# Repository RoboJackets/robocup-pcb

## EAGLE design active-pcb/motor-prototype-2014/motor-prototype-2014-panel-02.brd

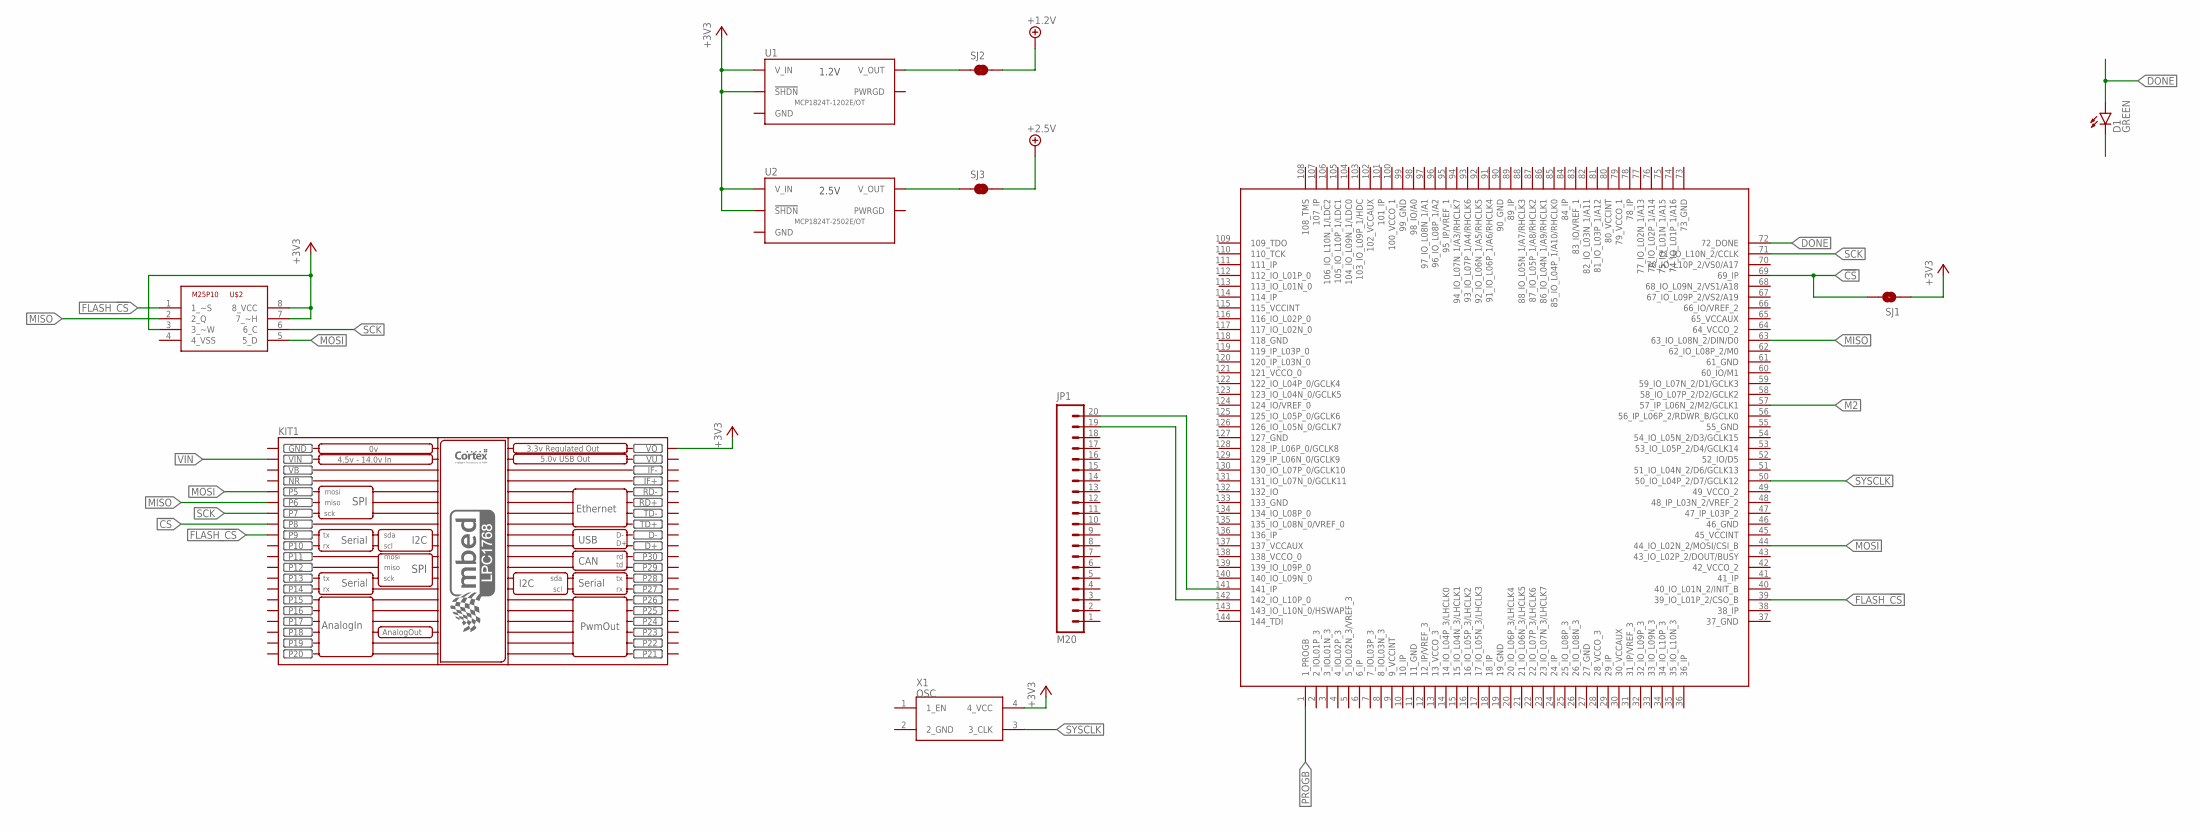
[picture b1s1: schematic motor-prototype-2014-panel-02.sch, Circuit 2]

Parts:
D1: GREEN; LED-0603
JP1: M20; 1X20
KIT1: MBED_NXP_LPC1768; MBED-KIT
SJ1: JUMPER-PAD-2-NO; PAD-JUMPER-2-NO_NO_SILK
SJ2, SJ3: JUMPER-PAD-2-NC_BY_TRACE; PAD-JUMPER-2-NC_BY_TRACE_YES_SILK
U1: MCP1824T-1202E/OT; SOT-23-5
U2: MCP1824T-2502E/OT; SOT-23-5
U$1: XC3S_TQ144; TQFP144
U$2: M25P10; SO08
X1: OSC; XTAL_LCC

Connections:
!CS!: KIT1.P$8 (P8), SJ1.2, U$1.69 (69_IP)
+1.2V: SJ2.2
+2.5V: SJ3.2
+3V3: KIT1.VOUT (VO), SJ1.1, U1.1 (V_IN), U1.3 (!SHDN), U2.1 (V_IN), U2.3 (!SHDN), U$2.3 (3_~W), U$2.7 (7_~H), U$2.8 (8_VCC), X1.4 (4_VCC)
DONE: D1.A, U$1.72 (72_DONE)
FLASH_!CS!: KIT1.P$9 (P9), U$1.39 (39_IO_L01P_2/CSO_B), U$2.1 (1_~S)
GND: KIT1.GND
M2: U$1.57 (57_IP_L06N_2/M2/GCLK1)
MISO: KIT1.P$6 (P6), U$1.63 (63_IO_L08N_2/DIN/D0), U$2.2 (2_Q)
MOSI: KIT1.P$5 (P5), U$1.44 (44_IO_L02N_2/MOSI/CSI_B), U$2.5 (5_D)
unnamed: JP1.20, U$1.141 (141_IP)
unnamed: JP1.19, U$1.142 (142_IO_L10P_0)
PROGB: U$1.1 (1_PROGB)
SCK: KIT1.P$7 (P7), U$1.71 (71_IO_L10N_2/CCLK), U$2.6 (6_C)
SYSCLK: U$1.50 (50_IO_L04P_2/D7/GCLK12), X1.3 (3_CLK)
VB: KIT1.VB
VIN: KIT1.VIN
VU: KIT1.VU
V_OUT: SJ2.1, SJ3.1, U1.5 (V_OUT), U2.5 (V_OUT)

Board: 4 copper layers, 11 parts (2 on the bottom side), 11 nets, no tracks yet.

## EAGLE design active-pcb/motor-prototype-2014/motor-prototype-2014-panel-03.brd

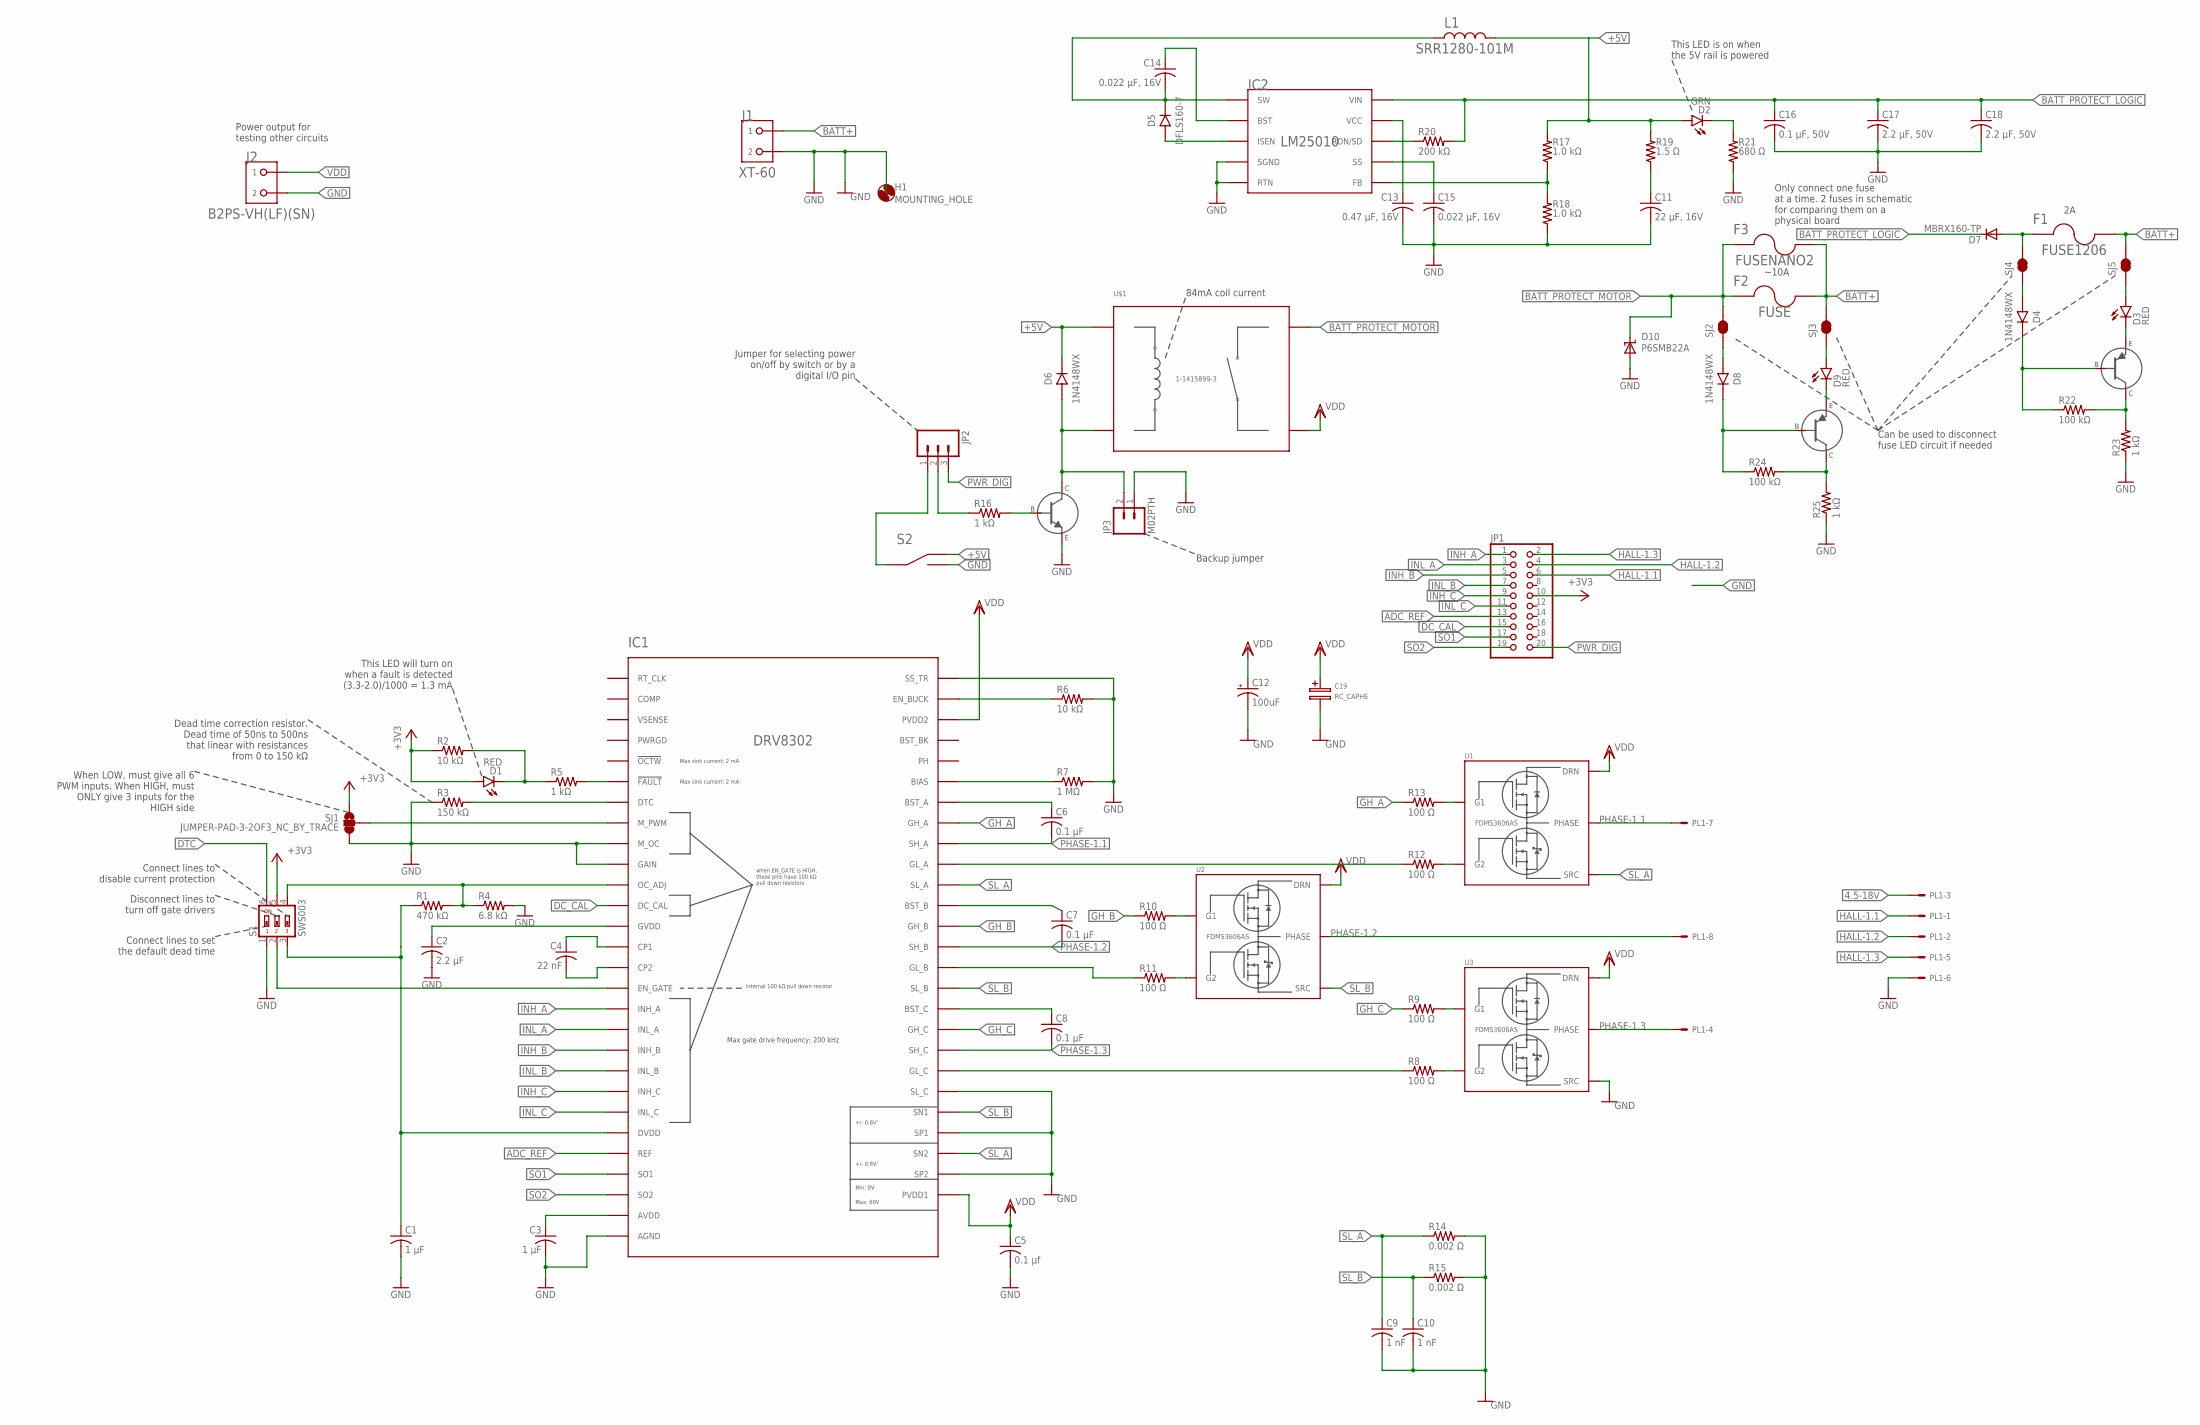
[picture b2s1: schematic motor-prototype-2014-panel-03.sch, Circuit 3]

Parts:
C1, C3: 1 µF; C0603
C2: 2.2 µF; C0603
C4: 22 nF; C1206
C5: 0.1 µf; C0603
C6, C7, C8: 0.1 µF; C0402
C9, C10: 1 nF; C0402
C11: 22 µF, 16V; C0402
C12: 100uF; PANASONIC_H13
C13: 0.47 µF, 16V; C0402
C14, C15: 0.022 µF, 16V; C0402
C16: 0.1 µF, 50V; C0603
C17, C18: 2.2 µF, 50V; C0603
C19: RC_CAPHE; HE_SERIES
D1, D3, D9: RED; LED-0603
D2: GRN; LED-0603
D4, D6, D8: 1N4148WX; SOD-323
D5: DFLS160-7; POWERDI-123
D7: MBRX160-TP; SOD123
D10: P6SMB22A; SMBJ
F1: FUSE1206; F1206
F2: FUSE; FUSE_MINI_ATC
F3: FUSENANO2; NANO2_157
H1: MOUNTING_HOLE
IC1: DRV8302; TSSOP-56_3
IC2: LM25010; 10-WDFN
J1: XT-60
J2: B2PS-VH(LF)(SN); B2PS
JP1: PINHD-2X10; 2X10
JP2: M03PTH; 1X03
JP3: M02PTH; 1X02
L1: SRR1280-101M; SRR1280
PL1: 555X-8V; 5566-8
Q1, Q3: BJT-PNP_; SOT-23-3
Q2: MMBT2222A-TP; SOT-23-3
R1: 470 kΩ; R0402
R2, R6: 10 kΩ; R0402
R3: 150 kΩ; R0603
R4: 6.8 kΩ; R0402
R5, R16, R23, R25: 1 kΩ; R0402
R7: 1 MΩ; R0402
R8, R9, R10, R11, R12, R13: 100 Ω; R0402
R14, R15: 0.002 Ω; R1206
R17, R18: 1.0 kΩ; R0402
R19: 1.5 Ω; R0402
R20: 200 kΩ; R0402
R21: 680 Ω; R0402
R22, R24: 100 kΩ; R0402
S1: SWS003; SMS-003
S2: 34EWMSP12MRT; 34EWMSP12M6RT
SJ1: JUMPER-PAD-3-2OF3_NC_BY_TRACE; PAD-JUMPER-3-2OF3_NC_BY_TRACE_YES_SILK_FULL_BOX
SJ2, SJ3, SJ4, SJ5: JUMPER-PAD-2-NC_BY_TRACE; PAD-JUMPER-2-NC_BY_TRACE_YES_SILK
U1, U2, U3: FDMS3606AS; PQFN-(DUAL)
U$1: 1-1415899-3

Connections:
4.5-18V: PL1.3
!FAULT!: IC1.6 (!FAULT!), R5.2
+3V3: D1.A, JP1.10, R2.1, S1.5, SJ1.1
+5V: D2.A, D6.C, L1.P$1, R17.2, R19.2, S2.1 (OFF), U$1.A1 (2)
ADC_REF: IC1.24 (REF), JP1.13
BATT+: F1.2, F2.2.1 (2), F2.2.2 (2), F3.P$2 (2), J1.BATT (1), SJ3.2, SJ5.2
BATT_PROTECT_LOGIC: C16.1, C17.1, C18.1, D7.C, IC2.P10.1 (VIN), IC2.P10.2 (VIN), R20.2
BATT_PROTECT_MOTOR: D10.C, F2.1.1 (1), F2.1.2 (1), F3.P$1 (1), SJ2.2, U$1.14.1 (3), U$1.14.2 (3)
BIAS: IC1.49 (BIAS), R7.1
BOB: D7.A, F1.1, SJ4.2
BST_A: C6.1, IC1.48 (BST_A)
BST_B: C7.1, IC1.43 (BST_B)
BST_BK: IC1.52 (BST_BK)
BST_C: C8.1, IC1.38 (BST_C)
CP1: C4.1, IC1.14 (CP1)
CP2: C4.2, IC1.15 (CP2)
DC_CAL: IC1.12 (DC_CAL), JP1.15
DTC: IC1.7 (DTC), R3.2, S1.6
GH_A: IC1.47 (GH_A), R13.1
GH_A_F: R13.2, U1.1 (G1)
GH_B: IC1.42 (GH_B), R10.1
GH_B_F: R10.2, U2.1 (G1)
GH_C: IC1.37 (GH_C), R9.1
GH_C_F: R9.2, U3.1 (G1)
GL_A: IC1.45 (GL_A), R12.1
GL_A_F: R12.2, U1.8 (G2)
GL_B: IC1.40 (GL_B), R11.1
GL_B_F: R11.2, U2.8 (G2)
GL_C: R8.2, U3.8 (G2)
GND: C1.2, C2.2, C3.2, C5.2, C9.2, C10.2, C11.2, C12.-, C13.2, C15.2, C16.2, C17.2, C18.2, C19.NEG (-), D10.A, H1.GND, IC1.9 (M_OC), IC1.10 (GAIN), IC1.28 (AGND), IC1.30 (SP2), IC1.32 (SP1), IC1.34 (SL_C), IC1.56 (SS_TR), IC1.57 (AGND), IC1.58 (AGND), IC1.59 (AGND), IC2.P4.1 (SGND), IC2.P4.2 (SGND), IC2.P5.1 (RTN), IC2.P5.2 (RTN), IC2.P_CENTER (SGND), J1.GND (2), J2.2, JP3.1, PL1.6, Q2.S (E), R3.1, R4.2, R6.2, R7.2, R14.2, R15.2, R18.1, R21.1, R23.1, R25.1, S1.1, S2.3 (ON), SJ1.3, U3.5 (SRC), U3.6 (SRC), U3.7 (SRC)
HALL-1.1: JP1.6, PL1.1
HALL-1.2: JP1.4, PL1.2
HALL-1.3: JP1.2, PL1.5
INH_A: IC1.17 (INH_A), JP1.1
INH_B: IC1.19 (INH_B), JP1.5
INH_C: IC1.21 (INH_C), JP1.9
INL_A: IC1.18 (INL_A), JP1.3
INL_B: IC1.20 (INL_B), JP1.7
INL_C: IC1.22 (INL_C), JP1.11
M_PWM: IC1.8 (M_PWM), SJ1.2
unnamed: D1.C, R2.2, R5.1
unnamed: C15.1, IC2.P7.1 (SS), IC2.P7.2 (SS)
unnamed: JP2.2, R16.1
unnamed: IC1.35 (GL_C), R8.1
unnamed: D5.A, IC2.P3.1 (ISEN), IC2.P3.2 (ISEN)
unnamed: C13.1, IC2.P9.1 (VCC), IC2.P9.2 (VCC)
unnamed: D4.C, Q1.G (B), R22.1
unnamed: IC1.11 (OC_ADJ), R1.2, R4.1, S1.4
unnamed: IC2.P6.1 (FB), IC2.P6.2 (FB), R17.1, R18.2
unnamed: C2.1, IC1.13 (GVDD)
unnamed: C1.1, IC1.23 (DVDD), R1.1, S1.3
unnamed: IC1.55 (EN_BUCK), R6.1
unnamed: IC1.16 (EN_GATE), S1.2
unnamed: C3.1, IC1.27 (AVDD)
unnamed: D3.C, Q1.S (E)
unnamed: IC2.P8.1 (RON/SD), IC2.P8.2 (RON/SD), R20.1
unnamed: Q1.D (C), R22.2, R23.2
unnamed: C11.1, R19.1
unnamed: D9.C, Q3.S (E)
unnamed: C14.1, IC2.P2.1 (BST), IC2.P2.2 (BST)
unnamed: C14.2, D5.C, IC2.P1.1 (SW), IC2.P1.2 (SW), L1.P$2
unnamed: D6.A, JP3.2, Q2.D (C), U$1.A2 (6)
unnamed: D2.C, R21.2
unnamed: Q2.G (B), R16.2
unnamed: D8.C, Q3.G (B), R24.1
unnamed: Q3.D (C), R24.2, R25.2
unnamed: JP2.1, S2.2 (C)
unnamed: D8.A, SJ2.1
unnamed: D9.A, SJ3.1
unnamed: D4.A, SJ4.1
unnamed: D3.A, SJ5.1
PHASE-1.1: C6.2, IC1.46 (SH_A), PL1.7, U1.CENTER (PHASE)
PHASE-1.2: C7.2, IC1.41 (SH_B), PL1.8, U2.CENTER (PHASE)
PHASE-1.3: C8.2, IC1.36 (SH_C), PL1.4, U3.CENTER (PHASE)
PWR_DIG: JP1.20, JP2.3
SL_A: C9.1, IC1.31 (SN2), IC1.44 (SL_A), R14.1, U1.5 (SRC), U1.6 (SRC), U1.7 (SRC)
SL_B: C10.1, IC1.33 (SN1), IC1.39 (SL_B), R15.1, U2.5 (SRC), U2.6 (SRC), U2.7 (SRC)
SO1: IC1.25 (SO1), JP1.17
SO2: IC1.26 (SO2), JP1.19
VDD: C5.1, C12.+, C19.POS (+), IC1.29 (PVDD1), IC1.53 (PVDD2), IC1.54 (PVDD2), J2.1, U1.2 (DRN), U1.3 (DRN), U1.4 (DRN), U1.LARGE_1 (DRN), U1.LARGE_2 (DRN), U1.LARGE_3 (DRN), U2.2 (DRN), U2.3 (DRN), U2.4 (DRN), U2.LARGE_1 (DRN), U2.LARGE_2 (DRN), U2.LARGE_3 (DRN), U3.2 (DRN), U3.3 (DRN), U3.4 (DRN), U3.LARGE_1 (DRN), U3.LARGE_2 (DRN), U3.LARGE_3 (DRN), U$1.11.1 (5), U$1.11.2 (5)

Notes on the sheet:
Connect lines to disable current protection
Dead time correction resistor. Dead time of 50ns to 500ns that linear with resistances from 0 to 150 kΩ
Disconnect lines to turn off gate drivers
Connect lines to set the default dead time
This LED is on when the 5V rail is powered
This LED will turn on when a fault is detected (3.3-2.0)/1000 = 1.3 mA
When LOW, must give all 6 PWM inputs. When HIGH, must ONLY give 3 inputs for the HIGH side
84mA coil current
Backup jumper
Jumper for selecting power on/off by switch or by a digital I/O pin
Can be used to disconnect fuse LED circuit if needed
~10A
Only connect one fuse at a time. 2 fuses in schematic for comparing them on a physical board
Power output for testing other circuits

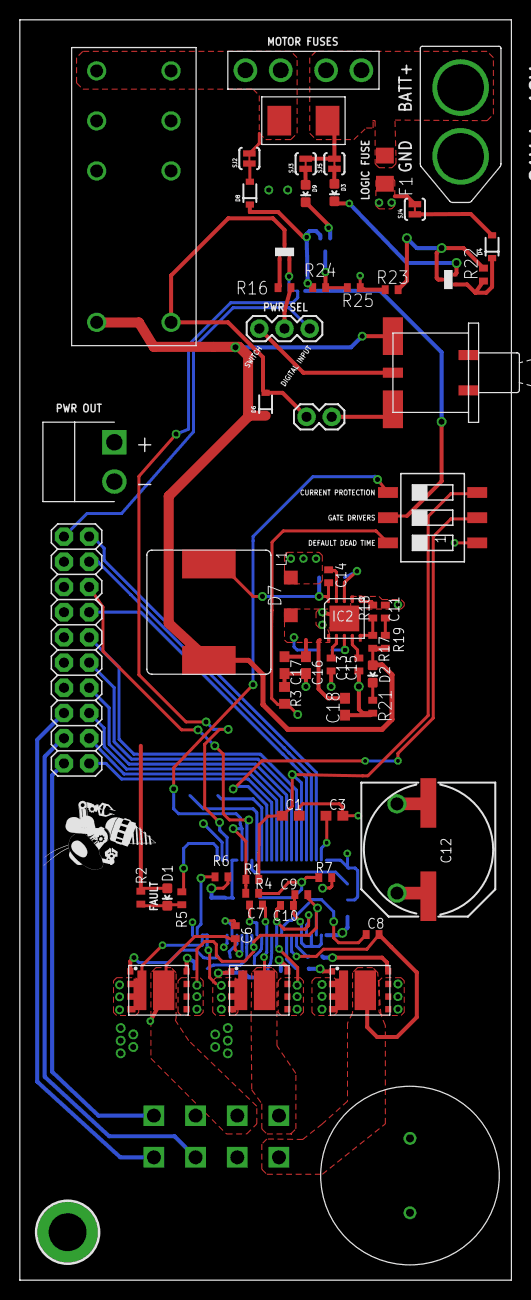
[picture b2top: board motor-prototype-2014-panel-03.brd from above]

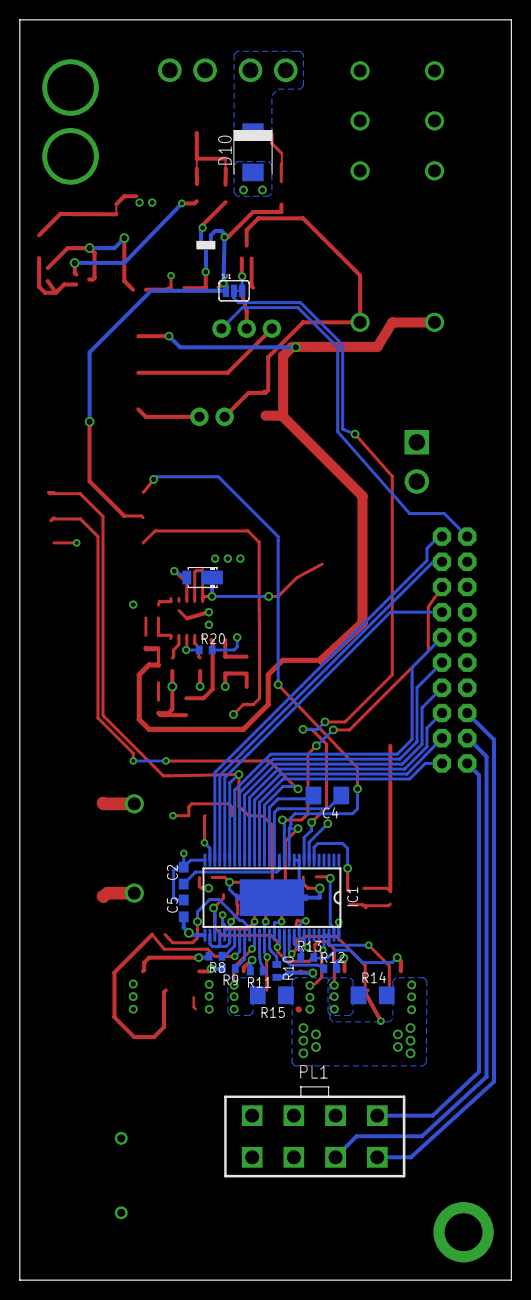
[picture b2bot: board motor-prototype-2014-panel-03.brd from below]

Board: 4 copper layers, 49.5 x 127.0 mm, 82 parts (18 on the bottom side), 78 nets.

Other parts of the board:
U$2: ROBOBUZZ_0.6X

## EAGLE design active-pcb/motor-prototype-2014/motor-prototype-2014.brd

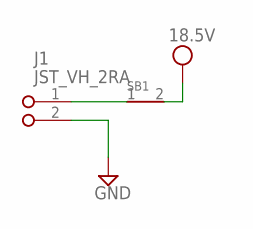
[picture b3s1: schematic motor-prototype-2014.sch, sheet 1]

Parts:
J1: JST_VH_2RA; JST_VH_2_RA
SB1: SOLDERBRIDGESB1206; SB1206

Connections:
GND: J1.2; also elsewhere on the board
VCC: SB1.2; also elsewhere on the board
V_IN: J1.1, SB1.1

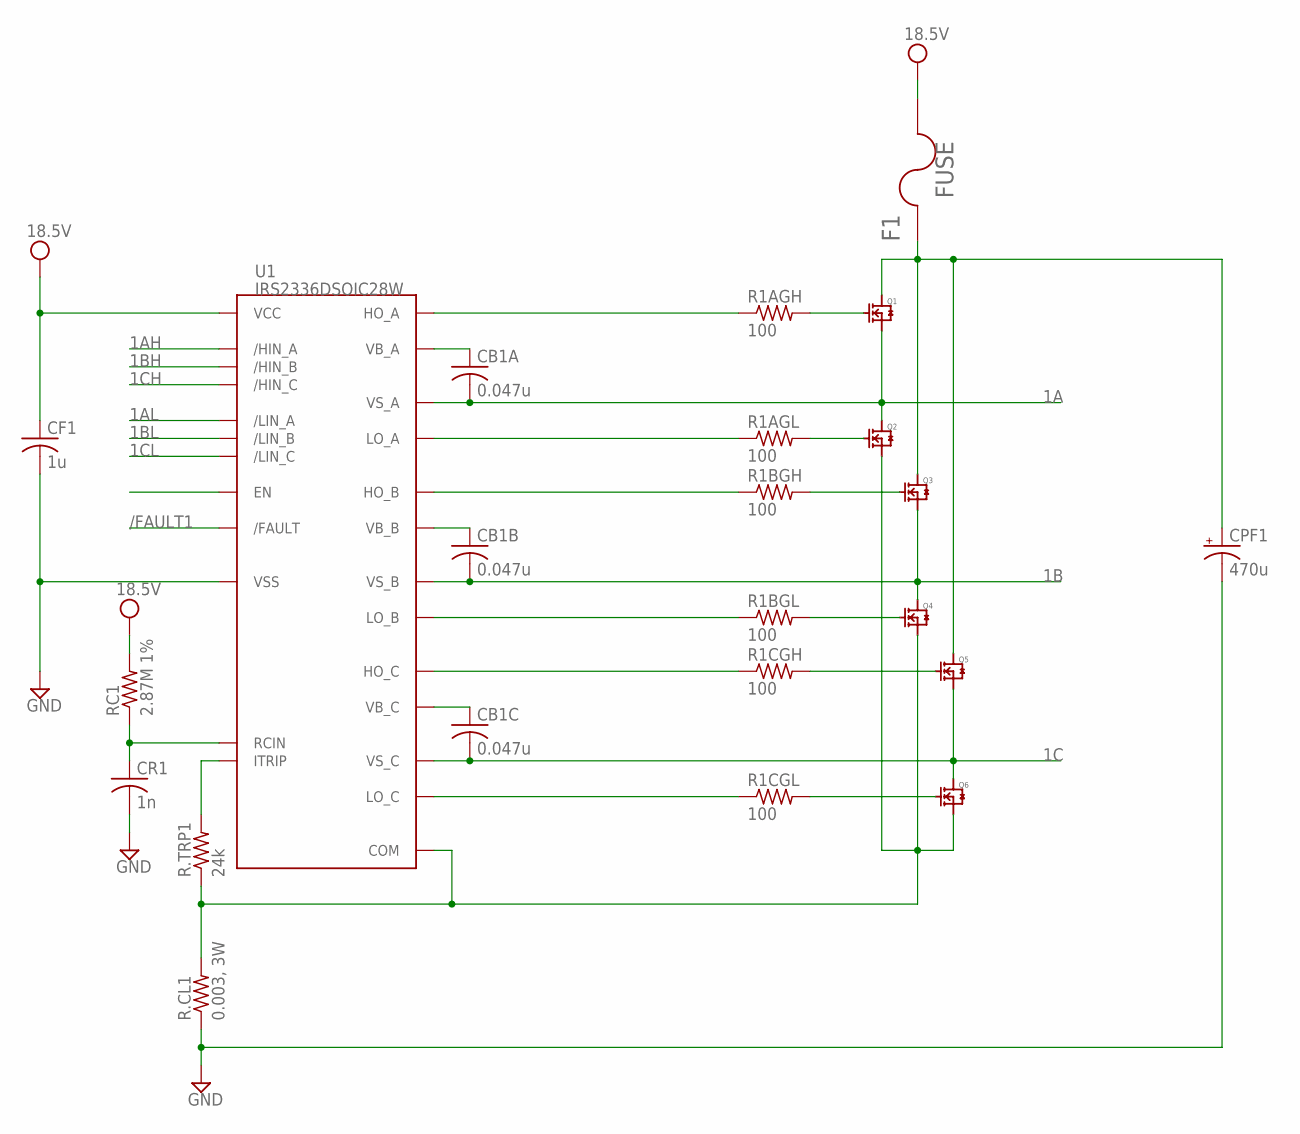
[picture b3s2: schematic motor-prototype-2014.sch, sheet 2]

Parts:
CB1A, CB1B, CB1C: 0.047u; C1206
CF1: 1u; C0603
CPF1: 470u; PANASONIC_G
CR1: 1n; C0603
F1: FUSE; FUSE_MINI_ATC
Q1, Q2, Q3, Q4, Q5, Q6: SIR438DP; POWERPAK_SO8
R1AGH, R1AGL, R1BGH, R1BGL, R1CGH, R1CGL: 100; R0603
R.CL1: 0.003, 3W; R2512
R.TRP1: 24k; R0603
RC1: 2.87M 1%; R0603
U1: IRS2336DSOIC28W; SO-28W

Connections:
1A: CB1A.2, Q1.1 (S), Q1.2 (S), Q1.3 (S), Q2.5 (D), U1.26 (VS_A)
1AH: U1.2 (/HIN_A)
1AL: U1.5 (/LIN_A)
1B: CB1B.2, Q3.1 (S), Q3.2 (S), Q3.3 (S), Q4.5 (D), U1.22 (VS_B)
1BH: U1.3 (/HIN_B)
1BL: U1.6 (/LIN_B)
1C: CB1C.2, Q5.1 (S), Q5.2 (S), Q5.3 (S), Q6.5 (D), U1.18 (VS_C)
1CH: U1.4 (/HIN_C)
1CL: U1.7 (/LIN_C)
/FAULT1: U1.8 (/FAULT)
GND: CF1.2, CPF1.-, CR1.2, R.CL1.1, U1.12 (VSS); also elsewhere on the board
unnamed: R1AGH.1, U1.27 (HO_A)
unnamed: Q1.4 (G), R1AGH.2
unnamed: Q2.4 (G), R1AGL.2
unnamed: R1AGL.1, U1.16 (LO_A)
unnamed: R1BGH.1, U1.23 (HO_B)
unnamed: R1BGL.1, U1.15 (LO_B)
unnamed: R1CGL.1, U1.14 (LO_C)
unnamed: R1CGH.1, U1.19 (HO_C)
unnamed: Q3.4 (G), R1BGH.2
unnamed: Q5.4 (G), R1CGH.2
unnamed: Q6.4 (G), R1CGL.2
unnamed: Q4.4 (G), R1BGL.2
unnamed: CR1.1, RC1.1, U1.11 (RCIN)
unnamed: R.TRP1.2, U1.9 (ITRIP)
PGND_1: Q2.1 (S), Q2.2 (S), Q2.3 (S), Q4.1 (S), Q4.2 (S), Q4.3 (S), Q6.1 (S), Q6.2 (S), Q6.3 (S), R.CL1.2, R.TRP1.1, U1.13 (COM)
VB_1A: CB1A.1, U1.28 (VB_A)
VB_1B: CB1B.1, U1.24 (VB_B)
VB_1C: CB1C.1, U1.20 (VB_C)
VCC: CF1.1, F1.2.1 (2), F1.2.2 (2), RC1.2, U1.1 (VCC); also elsewhere on the board
VM1: CPF1.+, F1.1.1 (1), F1.1.2 (1), Q1.5 (D), Q3.5 (D), Q5.5 (D)

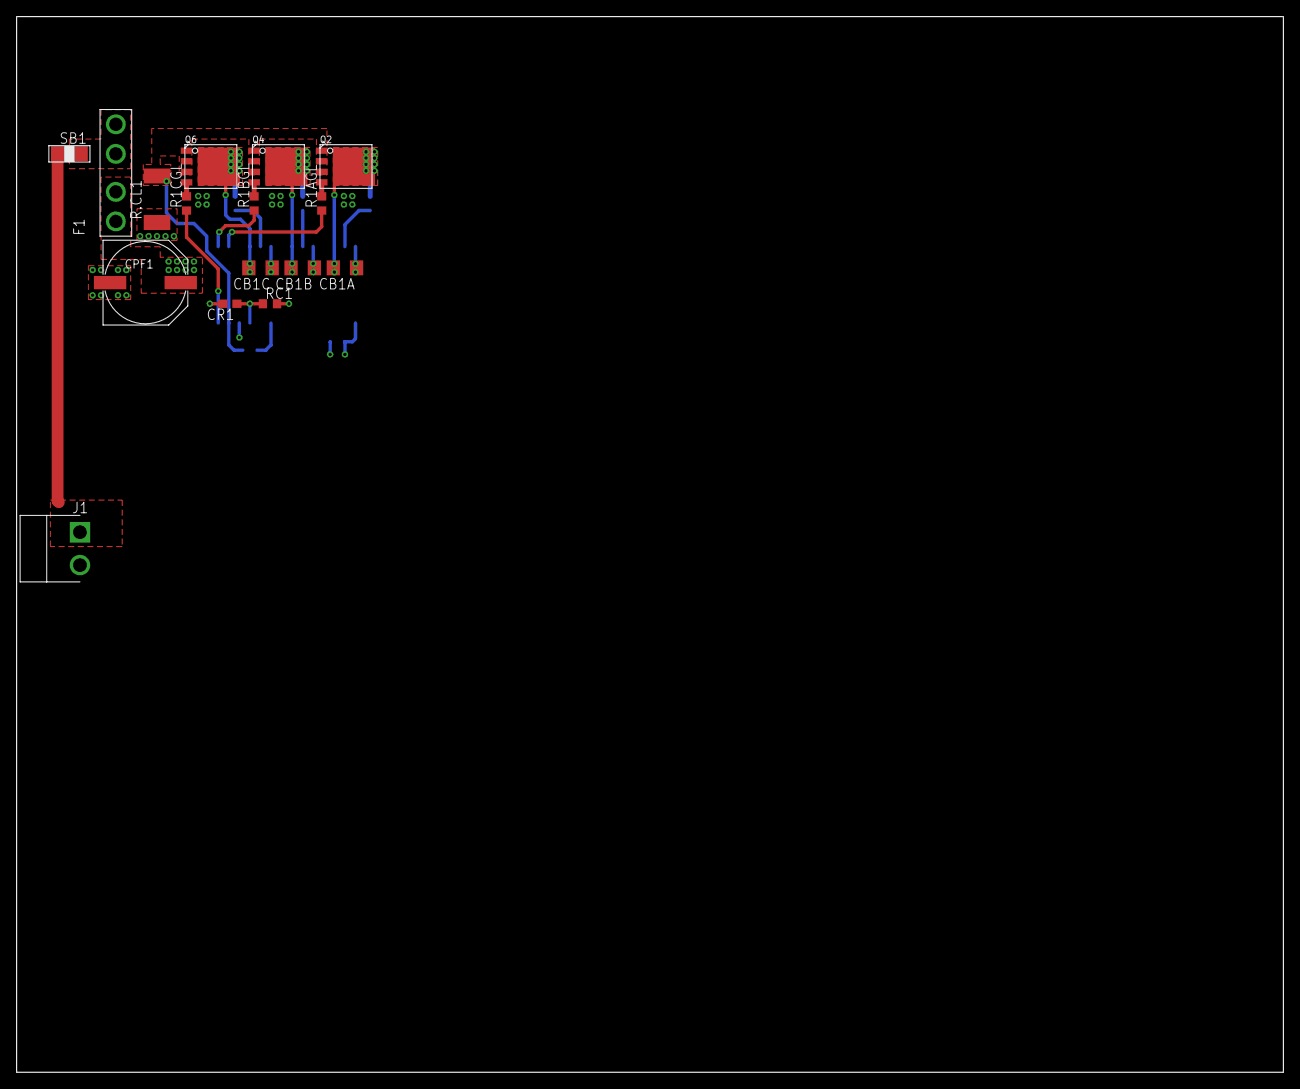
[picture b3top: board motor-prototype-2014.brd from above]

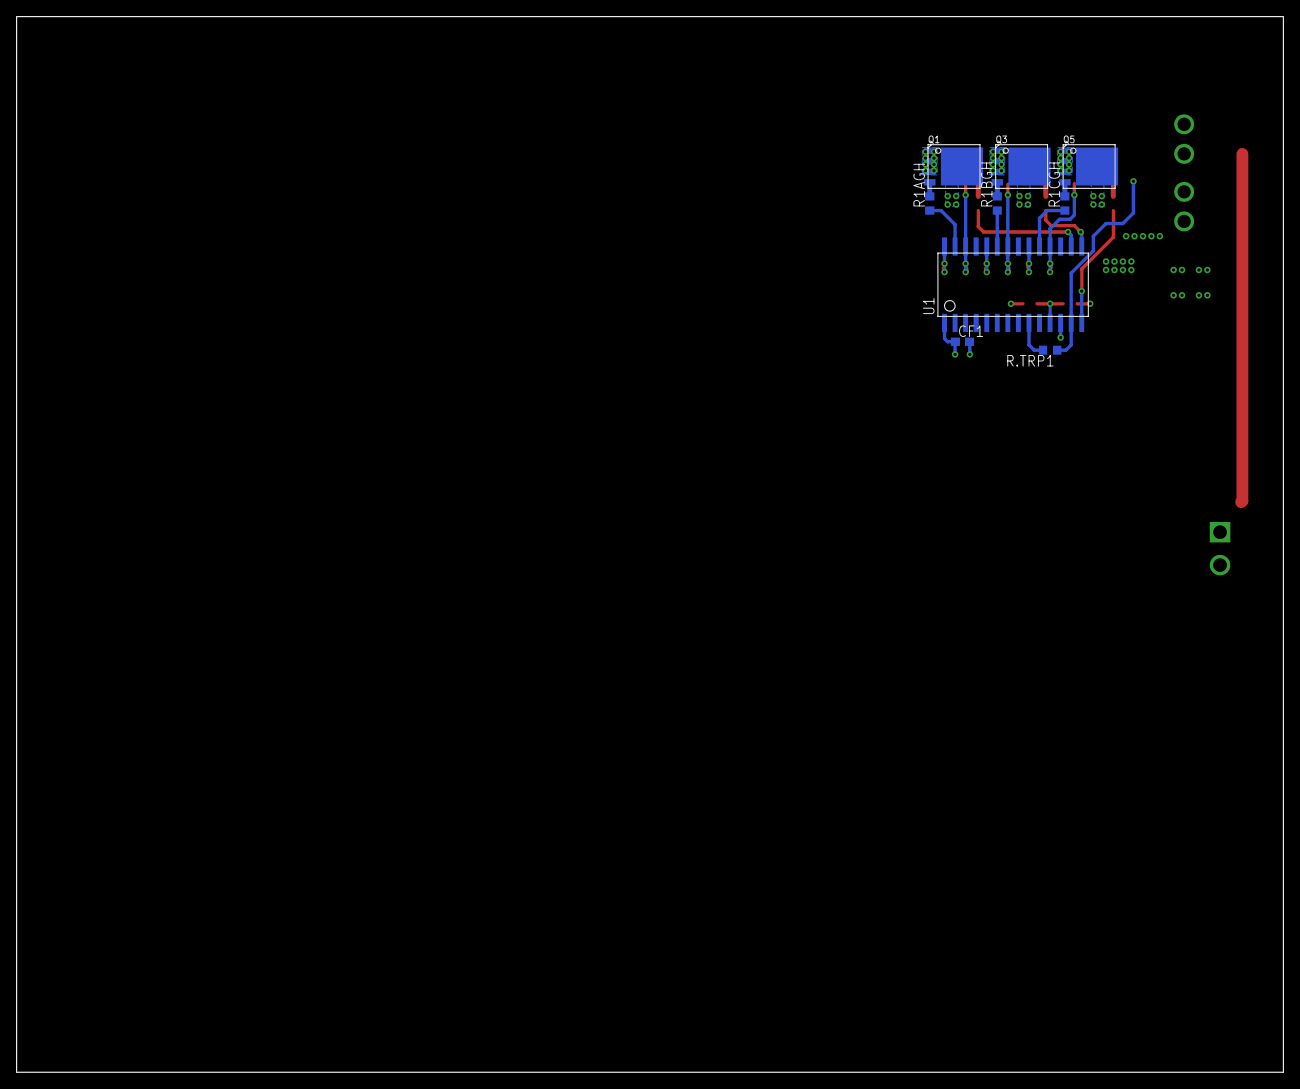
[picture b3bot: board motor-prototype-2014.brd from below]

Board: 4 copper layers, 152.4 x 127.0 mm, 25 parts (9 on the bottom side), 25 nets.

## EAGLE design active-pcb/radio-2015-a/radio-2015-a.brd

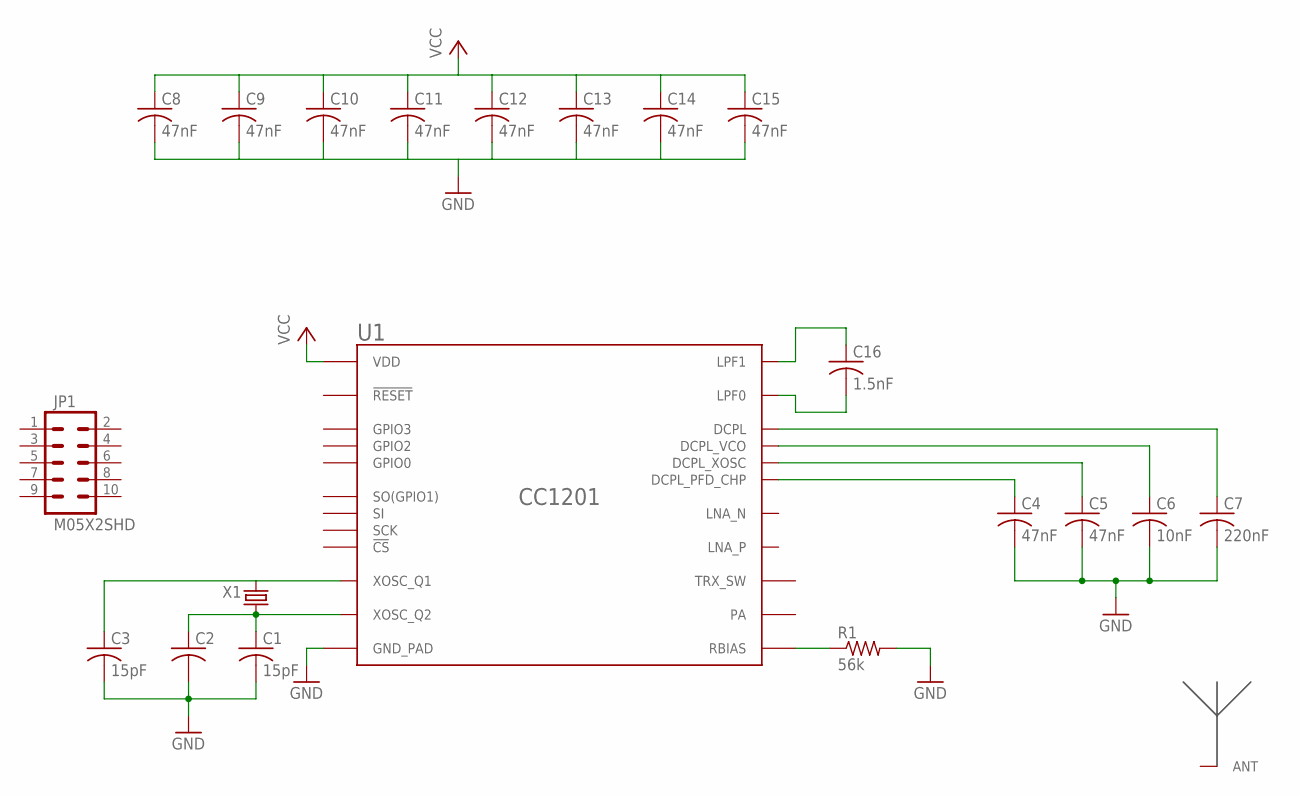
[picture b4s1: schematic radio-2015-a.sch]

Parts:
ANT1: ANT-916-CHP-T; ANT-916-CHP
C1, C3: 15pF; C0402
C2: C-USC0402; C0402
C4, C5, C8, C9, C10, C11, C12, C13, C14, C15: 47nF; C0402
C6: 10nF; C0402
C7: 220nF; C0402
C16: 1.5nF; C0402
JP1: M05X2SHD; 2X5-SHROUDED
R1: 56k; R0603
U1: CC1201; QFN-32
X1: XTAL-3.2X2.5

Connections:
GND: C1.2, C2.2, C3.2, C4.2, C5.2, C6.2, C7.2, C8.2, C9.2, C10.2, C11.2, C12.2, C13.2, C14.2, C15.2, R1.2, U1.P$33 (GND_PAD)
unnamed: C3.1, U1.P$30 (XOSC_Q1), X1.3 (2)
unnamed: C1.1, C2.1, U1.P$31 (XOSC_Q2), X1.1
unnamed: C4.1, U1.P$26 (DCPL_PFD_CHP)
unnamed: C5.1, U1.P$29 (DCPL_XOSC)
unnamed: C6.1, U1.P$21 (DCPL_VCO)
unnamed: C7.1, U1.P$6 (DCPL)
unnamed: R1.1, U1.P$14 (RBIAS)
unnamed: C16.1, U1.P$24 (LPF1)
unnamed: C16.2, U1.P$23 (LPF0)
VCC: C8.1, C9.1, C10.1, C11.1, C12.1, C13.1, C14.1, C15.1, U1.P$1 (VDD), U1.P$5 (VDD), U1.P$12 (VDD), U1.P$13 (VDD), U1.P$15 (VDD), U1.P$22 (VDD), U1.P$25 (VDD), U1.P$27 (VDD), U1.P$28 (VDD)

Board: 2 copper layers, 21 parts (1 on the bottom side), 11 nets, no tracks yet.

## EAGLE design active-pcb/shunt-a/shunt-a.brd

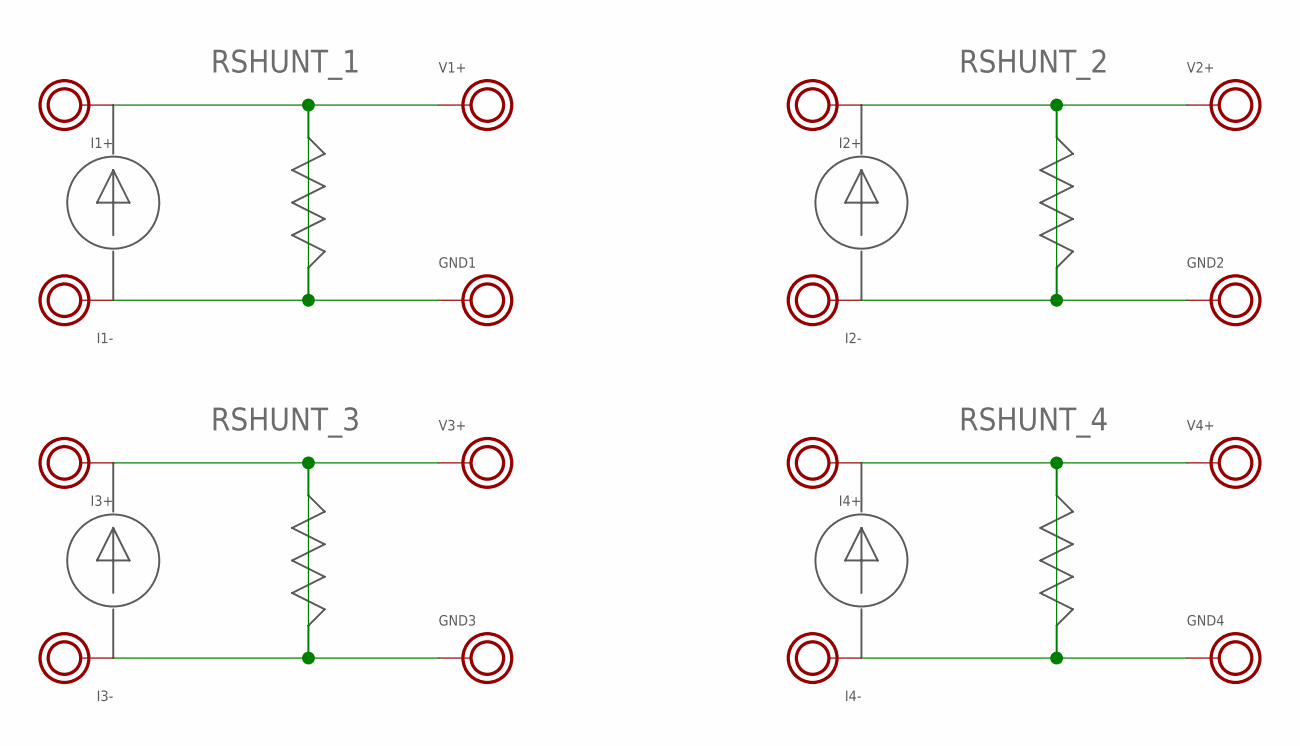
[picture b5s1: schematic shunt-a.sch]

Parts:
U$1: I1+; VIA_2MM
U$2: I1-; VIA_2MM
U$3: V1+; VIA_2MM
U$4: GND1; VIA_2MM
U$5: I2+; VIA_2MM
U$6: I2-; VIA_2MM
U$7: V2+; VIA_2MM
U$8: GND2; VIA_2MM
U$9: I3+; VIA_2MM
U$10: I3-; VIA_2MM
U$11: V3+; VIA_2MM
U$12: GND3; VIA_2MM
U$13: I4+; VIA_2MM
U$14: I4-; VIA_2MM
U$15: V4+; VIA_2MM
U$16: GND4; VIA_2MM

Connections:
RSHUNT_1: U$1.P$1, U$2.P$1, U$3.P$1, U$4.P$1
RSHUNT_2: U$5.P$1, U$6.P$1, U$7.P$1, U$8.P$1
RSHUNT_3: U$9.P$1, U$10.P$1, U$11.P$1, U$12.P$1
RSHUNT_4: U$13.P$1, U$14.P$1, U$15.P$1, U$16.P$1

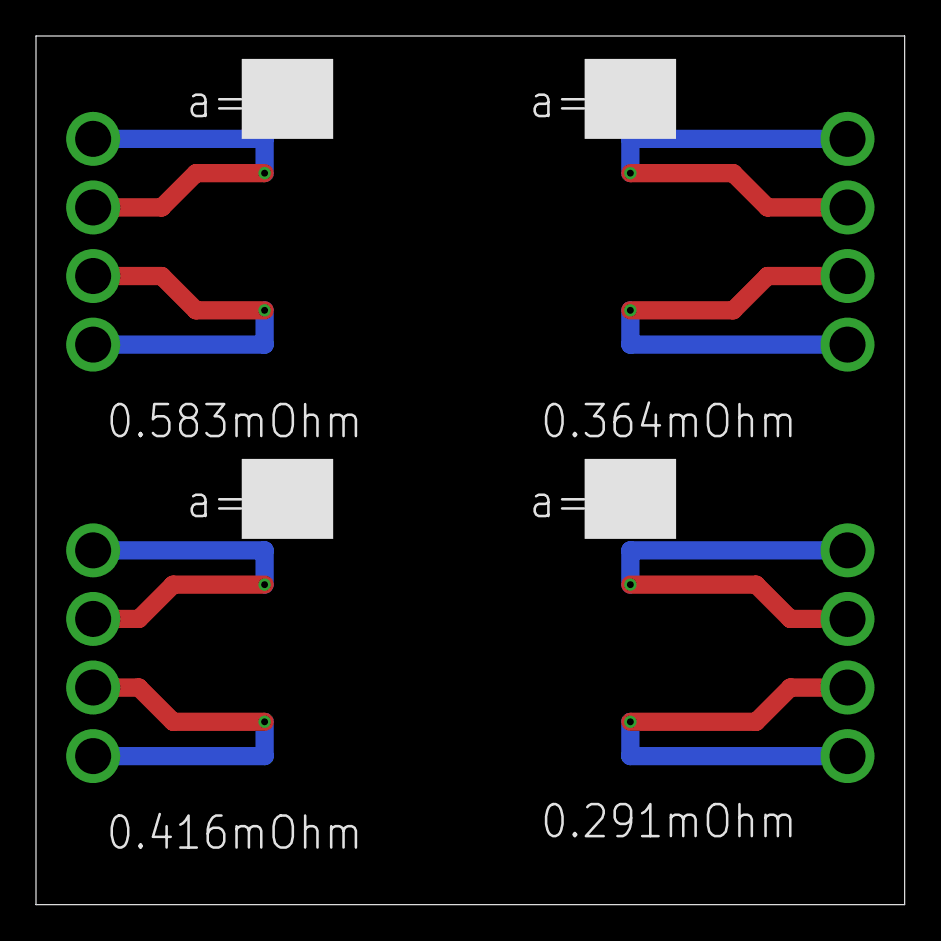
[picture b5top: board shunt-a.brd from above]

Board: 2 copper layers, 48.3 x 48.3 mm, 16 parts (0 on the bottom side), 4 nets.

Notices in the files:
parts and their libraries:
SparkFun-Passives: Licensing: Creative Commons ShareAlike 4.0 International - https://creativecommons.org/licenses/by-sa/4.0
